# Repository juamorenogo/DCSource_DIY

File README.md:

# EwigVolt - CV/CC Precision DC Supply

---

Electronic design project / UNAL / 2026-1
Project made by:
* Juan Sebastian Moreno Gonzalez
* Nicolás Prieto Solano

## Design Document

It is disposed a PDF file that contains every single detail of the design of this project.

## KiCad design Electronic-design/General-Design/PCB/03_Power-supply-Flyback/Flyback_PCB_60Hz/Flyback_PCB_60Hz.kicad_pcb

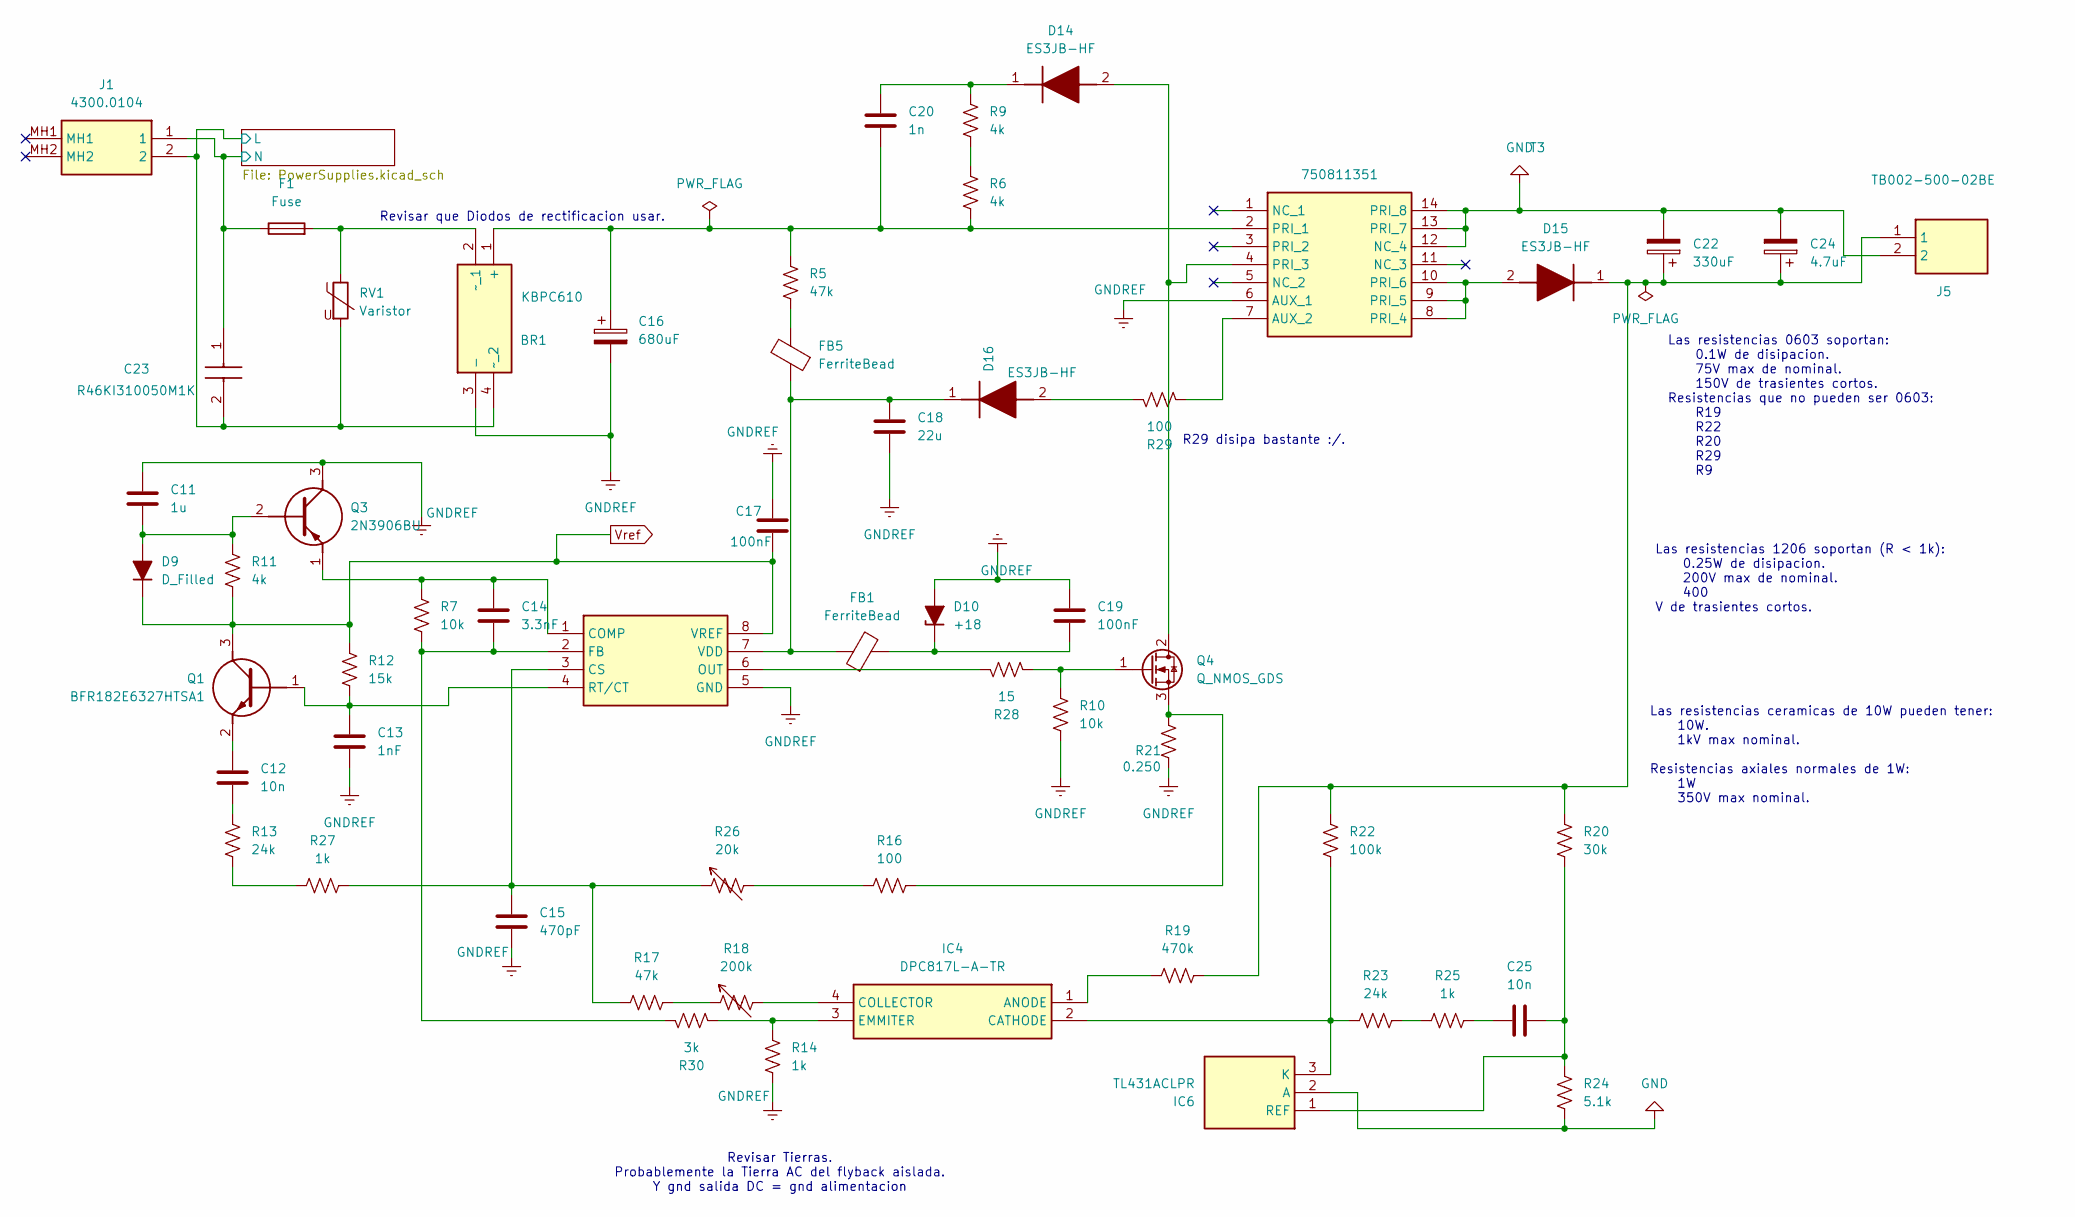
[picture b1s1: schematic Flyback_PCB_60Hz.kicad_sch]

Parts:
BR1: KBPC610; Mouser Part Number 637-KBPC610
C11: 1u; C_0805_2012Metric_Pad1.18x1.45mm_HandSolder
C12, C25: 10n; C_0805_2012Metric_Pad1.18x1.45mm_HandSolder
C13: 1nF; C_0805_2012Metric_Pad1.18x1.45mm_HandSolder
C14: 3.3nF; C_0805_2012Metric_Pad1.18x1.45mm_HandSolder
C15: 470pF; C_0805_2012Metric_Pad1.18x1.45mm_HandSolder
C16: 680uF; CP_Radial_D10.0mm_P5.00mm
C17, C19: 100nF; C_0805_2012Metric_Pad1.18x1.45mm_HandSolder
C18: 22u; CP_Radial_Tantal_D6.0mm_P2.50mm
C20: 1n; C_Disc_D7.5mm_W4.4mm_P5.00mm
C22: 330uF; CP_Radial_D18.0mm_P7.50mm
C23: R46KI310050M1K; Mouser Part Number 80-R46KI310050M1K
C24: 4.7uF; CP_Radial_D10.0mm_P5.00mm
D9: D_Filled; D_SMA_Handsoldering
D10: +18; D_DO-41_SOD81_P10.16mm_Horizontal
D14, D15, D16: ES3JB-HF; DIOM5235X244N; Mouser Part Number 750-ES3JB-HF
F1: Fuse; Fuseholder_Cylinder-5x20mm_Schurter_0031_8201_Horizontal_Op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
FB1, FB5: FerriteBead; BEADC1608X95N
IC4: DPC817L-A-TR; SOP254P1180X410-4N; Manufacturer_Part_Number DPC817L-A-TR
IC5: UCC38C43DR; SOIC127P600X175-8N; Mouser Part Number 595-UCC38C43DR
IC6: TL431ACLPR; Mouser Part Number 595-TL431ACLPR
J1: 4300.0104; 43000104; Mouser Part Number 693-4300.0104
J5: TB002-500-02BE; Mouser Part Number 490-TB002-500-02BE
Q1: BFR182E6327HTSA1; NPN_SOT95P240X110-3N; Manufacturer_Part_Number BFR182E6327HTSA1
Q3: 2N3906BU; Mouser Part Number 512-2N3906BU
Q4: Q_NMOS_GDS; TO-220F-3_Vertical
R5, R17: 47k; R_0603_1608Metric_Pad0.98x0.95mm_HandSolder
R6, R9: 4k; R_Axial_Power_L20.0mm_W6.4mm_P25.40mm
R7, R10: 10k; R_0603_1608Metric_Pad0.98x0.95mm_HandSolder
R11: 4k; R_0603_1608Metric_Pad0.98x0.95mm_HandSolder
R12: 15k; R_0603_1608Metric_Pad0.98x0.95mm_HandSolder
R13, R23: 24k; R_0603_1608Metric_Pad0.98x0.95mm_HandSolder
R14, R25, R27: 1k; R_0603_1608Metric_Pad0.98x0.95mm_HandSolder
R16: 100; R_1206_3216Metric_Pad1.30x1.75mm_HandSolder
R18: 200k; Potentiometer_Bourns_3296W_Vertical
R19: 470k; R_1206_3216Metric_Pad1.30x1.75mm_HandSolder
R20: 30k; R_Axial_DIN0414_L11.9mm_D4.5mm_P15.24mm_Horizontal
R21: 0.250; RESC6432X70N
R22: 100k; R_Axial_DIN0414_L11.9mm_D4.5mm_P15.24mm_Horizontal
R24: 5.1k; R_1206_3216Metric_Pad1.30x1.75mm_HandSolder
R26: 20k; Potentiometer_Bourns_3296W_Vertical
R28: 15; R_1206_3216Metric_Pad1.30x1.75mm_HandSolder
R29: 100; R_Axial_DIN0414_L11.9mm_D4.5mm_P15.24mm_Horizontal
R30: 3k; R_0603_1608Metric_Pad0.98x0.95mm_HandSolder
RV1: Varistor; RV_Disc_D15.5mm_W4.4mm_P7.5mm
T3: 750811351; Mouser Part Number 710-750811351

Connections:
/Supplies/L: BR1.4 (~_2), C23.2, J1.2, RV1.2; also elsewhere on the board
/Supplies/N: C23.1, F1.1, J1.1; also elsewhere on the board
GND: C22.2, C24.2, IC6.2 (A), J5.2, R24.2, T3.12 (NC_4), T3.13 (PRI_7), T3.14 (PRI_8); also elsewhere on the board
GNDREF: BR1.3 (-), C11.1, C13.2, C15.2, C16.2, C17.1, C18.2, C19.1, D10.2 (A), IC5.5 (GND), Q3.3 (C), R10.2, R14.2, R21.2, T3.6 (AUX_1)
unnamed: BR1.1 (+), C16.1, C20.2, R5.1, R6.2, T3.2 (PRI_1)
unnamed: BR1.2 (~_1), F1.2, RV1.1
unnamed: C12.2, R13.1
unnamed: C25.2, R25.1
unnamed: C11.2, D9.2 (A), Q3.2 (B), R11.1
unnamed: C19.2, D10.1 (K), FB1.2
unnamed: D14.2 (A), Q4.2 (D), T3.4 (PRI_3)
unnamed: C20.1, D14.1 (K), R9.1
unnamed: D15.2 (A), T3.8 (PRI_4), T3.9 (PRI_5), T3.10 (PRI_6)
unnamed: C22.1, C24.1, D15.1 (K), J5.1, R19.1, R20.1, R22.2
unnamed: D16.2 (A), R29.1
unnamed: C18.1, D16.1 (K), FB1.1, FB5.1, IC5.7 (VDD)
unnamed: FB5.2, R5.2
unnamed: IC4.1 (ANODE), R19.2
unnamed: IC4.2 (CATHODE), IC6.3 (K), R22.1, R23.2
unnamed: IC4.4 (COLLECTOR), R18.2
unnamed: IC4.3 (EMMITER), R14.1, R30.2
unnamed: C14.1, IC5.1 (COMP), Q3.1 (E), R7.1
unnamed: C15.1, IC5.3 (CS), R17.1, R26.1, R27.2
unnamed: C14.2, IC5.2 (FB), R7.2, R30.1
unnamed: IC5.6 (OUT), R28.1
unnamed: C13.1, IC5.4 (RT/CT), Q1.1 (B), R12.2
unnamed: C25.1, IC6.1 (REF), R20.2, R24.1
unnamed: C12.1, Q1.2 (E)
unnamed: Q4.1 (G), R10.1, R28.2
unnamed: Q4.3 (S), R16.2, R21.1
unnamed: R6.1, R9.2
unnamed: R13.2, R27.1
unnamed: R16.1, R26.2
unnamed: R17.2, R18.1
unnamed: R23.1, R25.2
unnamed: R29.2, T3.7 (AUX_2)
Vref: C17.2, D9.1 (K), IC5.8 (VREF), Q1.3 (C), R11.2, R12.1

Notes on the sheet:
Las resistencias 1206 soportan (R < 1k): 0.25W de disipacion. 200V max de nominal. 400 V de trasientes cortos.
Revisar Tierras. Probablemente la Tierra AC del flyback aislada. Y gnd salida DC = gnd alimentacion
Las resistencias ceramicas de 10W pueden tener: 10W. 1kV max nominal. Resistencias axiales normales de 1W: 1W 350V max nominal.
R29 disipa bastante :/.
Las resistencias 0603 soportan: 0.1W de disipacion. 75V max de nominal. 150V de trasientes cortos. Resistencias que no pueden ser 0603: R19 R22 R20 R29 R9
Revisar que Diodos de rectificacion usar.

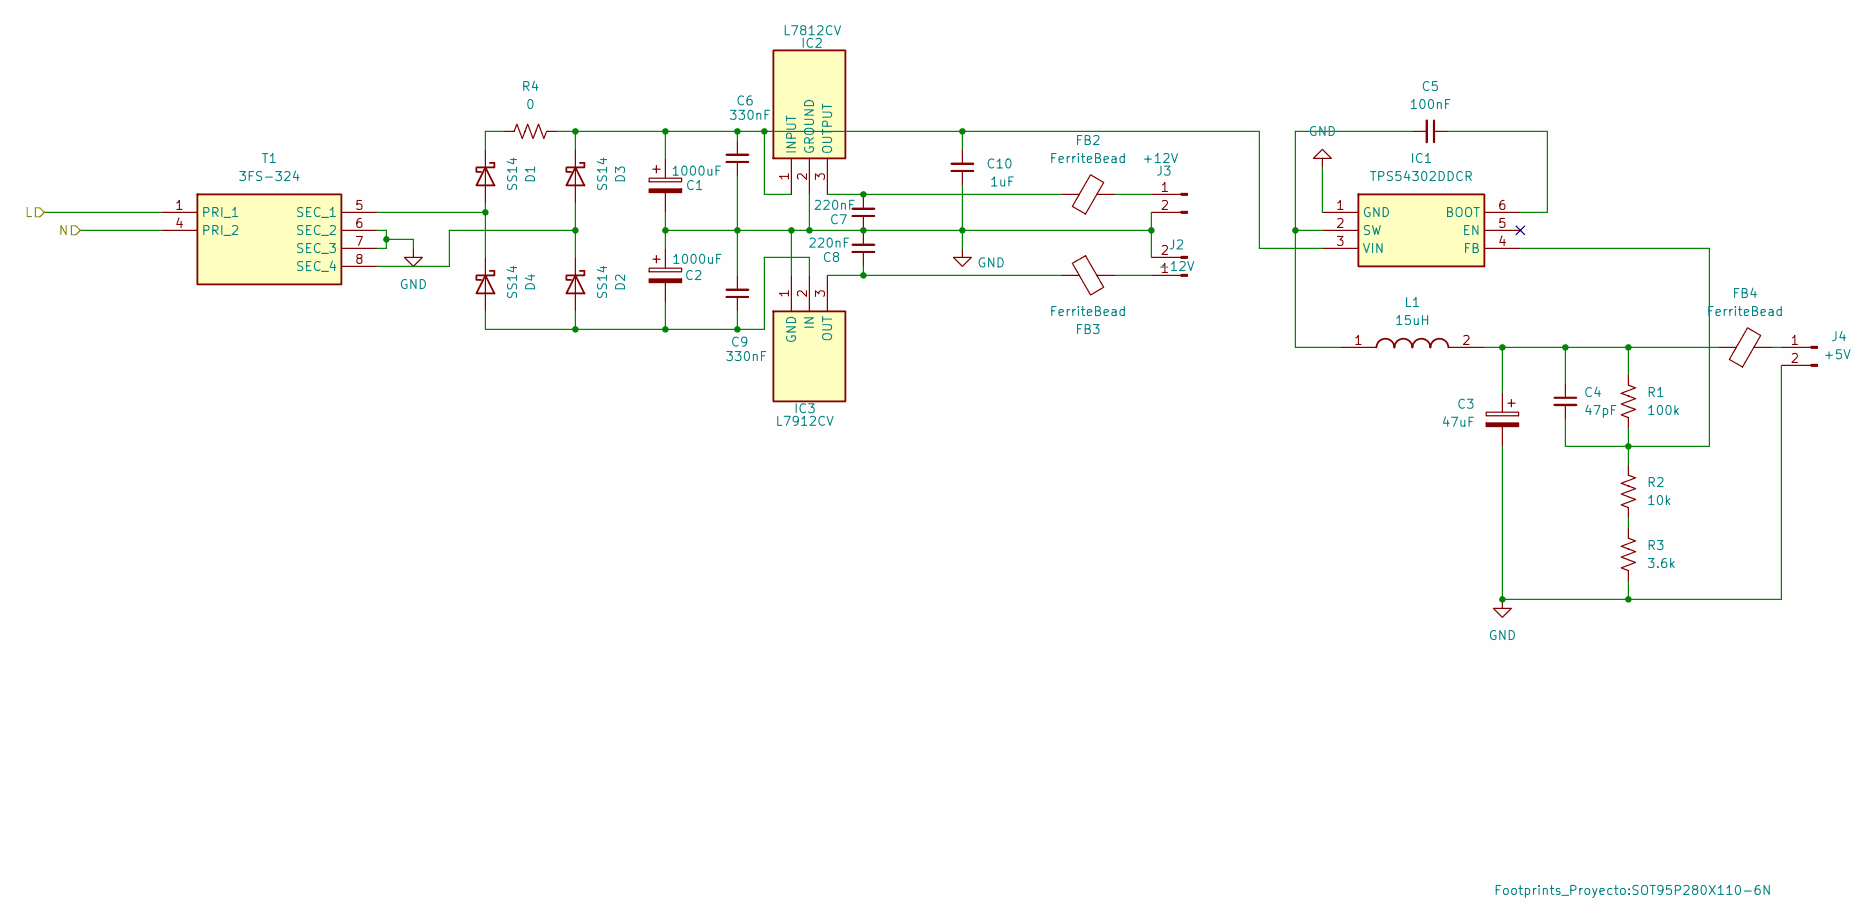
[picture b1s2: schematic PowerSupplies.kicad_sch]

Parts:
C1, C2: 1000uF; CP_Radial_D10.0mm_P5.00mm
C3: 47uF; CP_Radial_D6.3mm_P2.50mm
C4: 47pF; C_0805_2012Metric_Pad1.18x1.45mm_HandSolder
C5: 100nF; C_0805_2012Metric_Pad1.18x1.45mm_HandSolder
C6, C9: 330nF; C_0805_2012Metric_Pad1.18x1.45mm_HandSolder
C7, C8: 220nF; C_0805_2012Metric_Pad1.18x1.45mm_HandSolder
C10: 1uF; C_0805_2012Metric_Pad1.18x1.45mm_HandSolder
D1, D2, D3, D4: SS14; D_SMA
FB2, FB3, FB4: FerriteBead; BEADC1608X95N
IC1: TPS54302DDCR; SOT95P280X110-6N; Mouser Part Number 595-TPS54302DDCR
IC2: L7812CV; L8_TO255P460X1020X2008-3P; Mouser Part Number 511-L7812CV
IC3: L7912CV; L9_TO255P460X1020X2008-3P; Mouser Part Number 511-L7912CV
J2: -12V; PinHeader_1x02_P2.54mm_Vertical
J3: +12V; PinHeader_1x02_P2.54mm_Vertical
J4: +5V; PinHeader_1x02_P2.54mm_Vertical
L1: 15uH; INDPM116102X400N; Manufacturer_Part_Number AMRM00101040150MA1
R1: 100k; R_0603_1608Metric_Pad0.98x0.95mm_HandSolder
R2: 10k; R_0603_1608Metric_Pad0.98x0.95mm_HandSolder
R3: 3.6k; R_0603_1608Metric_Pad0.98x0.95mm_HandSolder
R4: 0; R_1210_3225Metric_Pad1.30x2.65mm_HandSolder
T1: 3FS-324; 3FS324; Mouser Part Number 838-3FS-324

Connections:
/Supplies/L: T1.1 (PRI_1); also elsewhere on the board
/Supplies/N: T1.4 (PRI_2); also elsewhere on the board
GND: C1.2, C2.1, C3.2, C6.1, C7.1, C8.2, C9.2, C10.1, IC1.1 (GND), IC2.2 (GROUND), IC3.1 (GND), J2.2, J3.2, J4.2, R3.2, T1.6 (SEC_2), T1.7 (SEC_3); also elsewhere on the board
unnamed: C3.1, C4.1, FB4.1, L1.2, R1.1
unnamed: D1.2 (A), D4.1 (K), T1.5 (SEC_1)
unnamed: D1.1 (K), R4.1
unnamed: C2.2, C9.1, D2.2 (A), D4.2 (A), IC3.2 (IN)
unnamed: D2.1 (K), D3.2 (A), T1.8 (SEC_4)
unnamed: C1.1, C6.2, C10.2, D3.1 (K), IC1.3 (VIN), IC2.1 (INPUT), R4.2
unnamed: C5.1, IC1.6 (BOOT)
unnamed: C4.2, IC1.4 (FB), R1.2, R2.1
unnamed: C5.2, IC1.2 (SW), L1.1
unnamed: C7.2, FB2.1, IC2.3 (OUTPUT)
unnamed: C8.1, FB3.1, IC3.3 (OUT)
unnamed: FB3.2, J2.1
unnamed: FB2.2, J3.1
unnamed: FB4.2, J4.1
unnamed: R2.2, R3.1

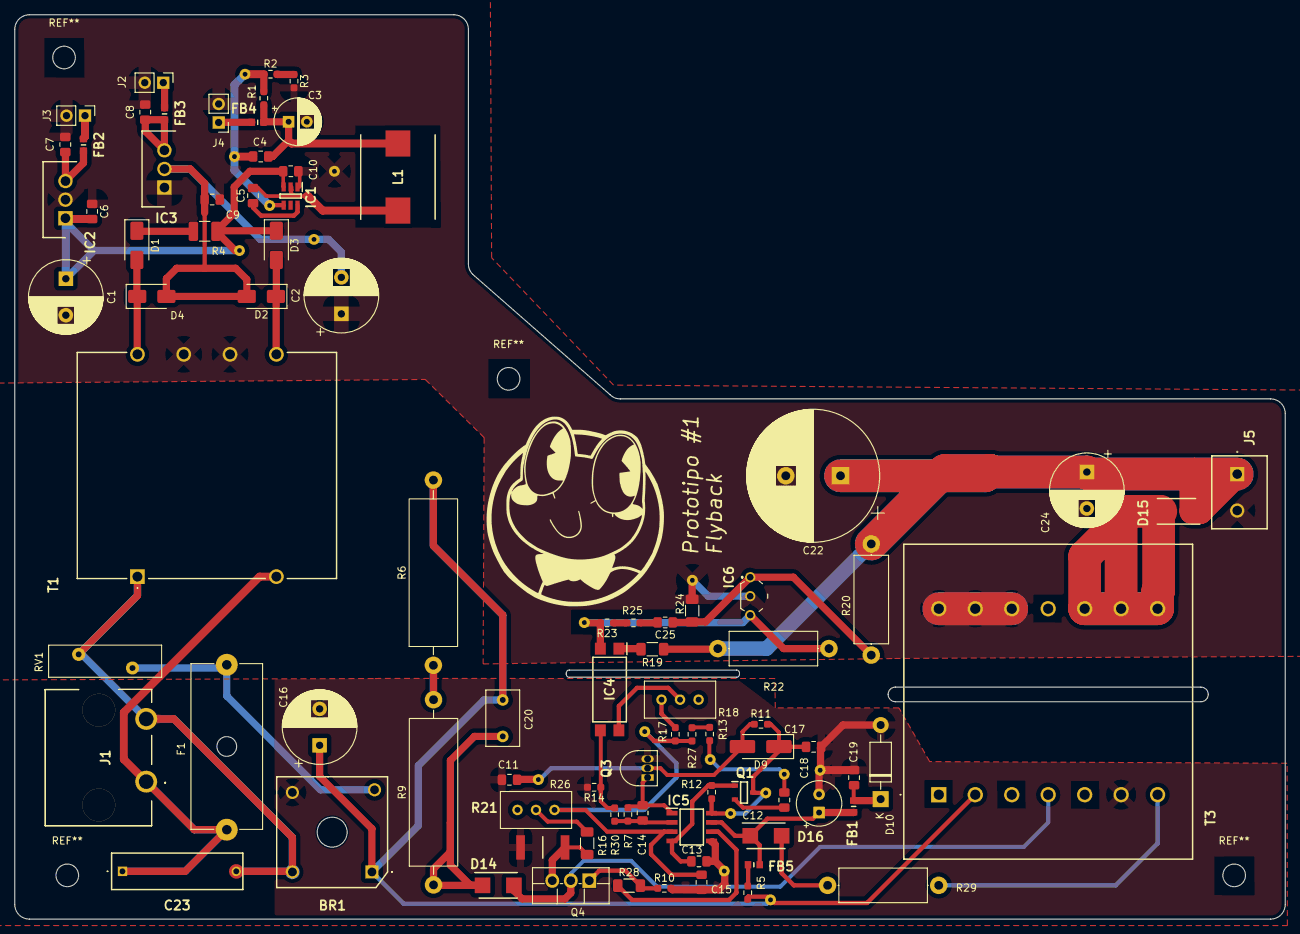
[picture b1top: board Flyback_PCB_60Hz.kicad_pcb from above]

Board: 2 copper layers, 174.2 x 124.0 mm, 86 parts (0 on the bottom side), 52 nets.

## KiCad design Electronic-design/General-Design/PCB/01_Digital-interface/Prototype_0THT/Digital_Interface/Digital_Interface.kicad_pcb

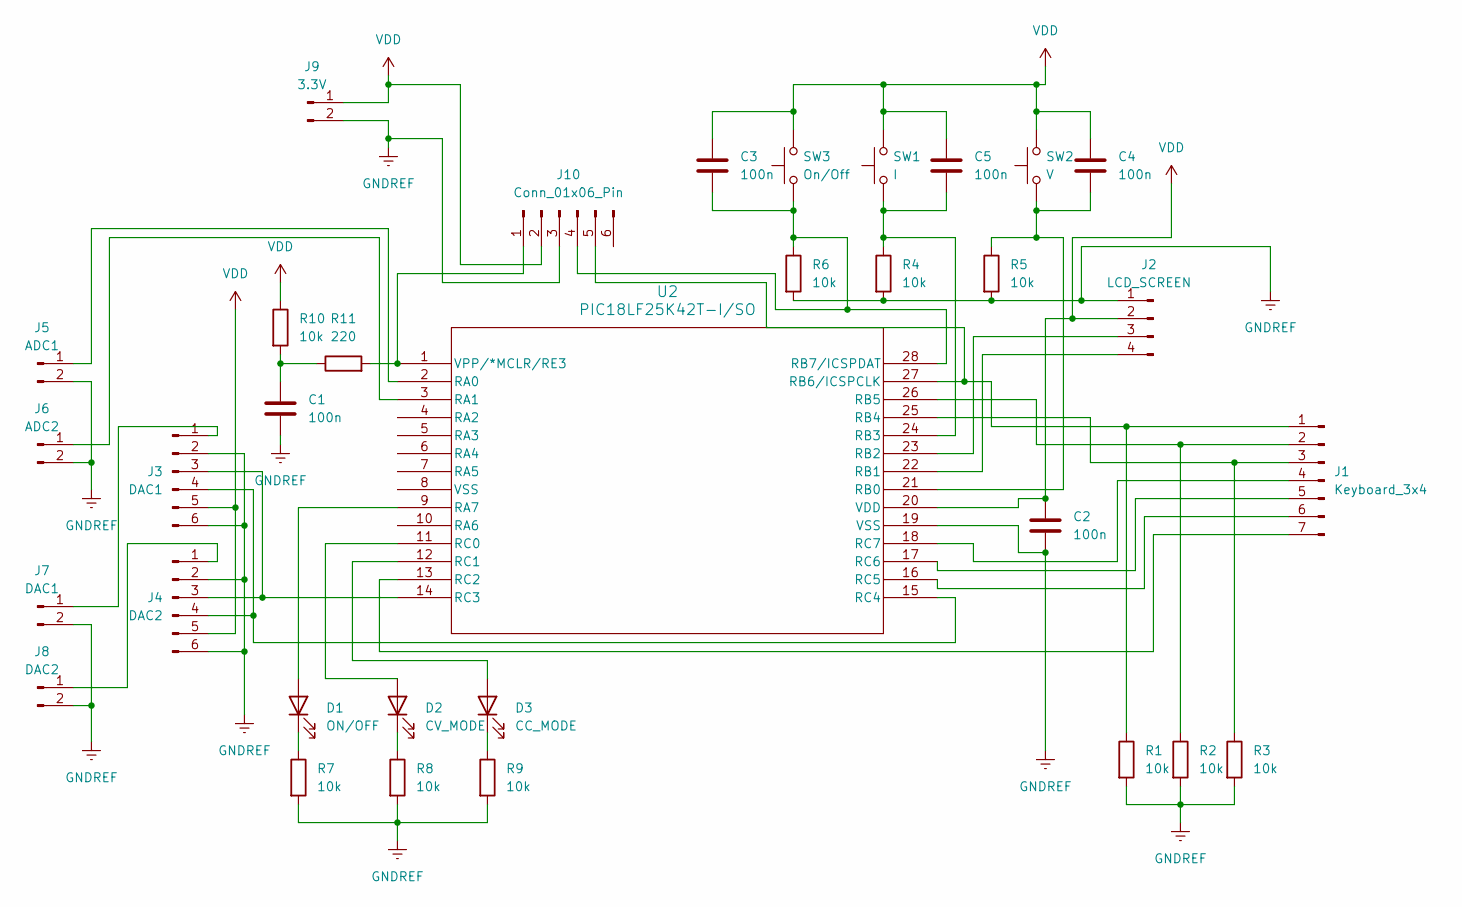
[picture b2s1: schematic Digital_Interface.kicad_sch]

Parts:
C1, C2, C3, C4, C5: 100n; C_Disc_D5.0mm_W2.5mm_P5.00mm
D1: ON/OFF; LED_D5.0mm
D2: CV_MODE; LED_D5.0mm
D3: CC_MODE; LED_D5.0mm
J1: Keyboard_3x4; PinHeader_1x07_P2.54mm_Vertical
J2: LCD_SCREEN; PinHeader_1x04_P2.54mm_Vertical
J3: DAC1; MCP4725_module
J4: DAC2; MCP4725_module
J5: ADC1; PinHeader_1x02_P2.54mm_Vertical
J6: ADC2; PinHeader_1x02_P2.54mm_Vertical
J7: DAC1; PinHeader_1x02_P2.54mm_Vertical
J8: DAC2; PinHeader_1x02_P2.54mm_Vertical
J9: 3.3V; PinHeader_1x02_P2.54mm_Vertical
J10: Conn_01x06_Pin; PinHeader_1x06_P2.54mm_Vertical
R1, R2, R3, R4, R5, R6, R7, R8, R9, R10: 10k; R_Axial_DIN0207_L6.3mm_D2.5mm_P7.62mm_Horizontal
R11: 220; R_Axial_DIN0207_L6.3mm_D2.5mm_P7.62mm_Horizontal
SW1: I; SW_PUSH_6mm
SW2: V; SW_PUSH_6mm
SW3: On/Off; SW_PUSH_6mm
U2: PIC18LF25K42T-I/SO; SOIC28_SO_MCH

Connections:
GNDREF: C1.2, C2.2, J2.1, J3.2, J3.6, J4.2, J4.6, J5.2, J6.2, J7.2, J8.2, J9.2, J10.3, R1.2, R2.2, R3.2, R4.2, R5.2, R6.2, R7.2, R8.2, R9.2, U2.19 (VSS)
unnamed: C1.1, R10.2, R11.1
unnamed: D1.2 (A), U2.9 (RA7)
unnamed: D1.1 (K), R7.1
unnamed: D2.2 (A), U2.11 (RC0)
unnamed: D2.1 (K), R8.1
unnamed: D3.2 (A), U2.12 (RC1)
unnamed: D3.1 (K), R9.1
unnamed: J1.1, J10.5, R1.1, U2.27 (RB6/ICSPCLK)
unnamed: J1.2, R2.1, U2.26 (RB5)
unnamed: J1.3, R3.1, U2.25 (RB4)
unnamed: J1.4, U2.18 (RC7)
unnamed: J1.5, U2.17 (RC6)
unnamed: J1.6, U2.16 (RC5)
unnamed: J1.7, U2.13 (RC2)
unnamed: J2.3, U2.23 (RB2)
unnamed: J2.4, U2.22 (RB1)
unnamed: J3.1, J7.1
unnamed: J3.3, J4.3, U2.14 (RC3)
unnamed: J3.4, J4.4, U2.15 (RC4)
unnamed: J4.1, J8.1
unnamed: J5.1, U2.2 (RA0)
unnamed: J6.1, U2.3 (RA1)
unnamed: J10.1, R11.2, U2.1 (VPP/*MCLR/RE3)
unnamed: C3.2, J10.4, R6.1, SW3.1, U2.28 (RB7/ICSPDAT)
unnamed: C4.2, R5.1, SW2.1, U2.21 (RB0)
unnamed: C5.2, R4.1, SW1.1, U2.24 (RB3)
VDD: C2.1, C3.1, C4.1, C5.1, J2.2, J3.5, J4.5, J9.1, J10.2, R10.1, SW1.2, SW2.2, SW3.2, U2.20 (VDD)

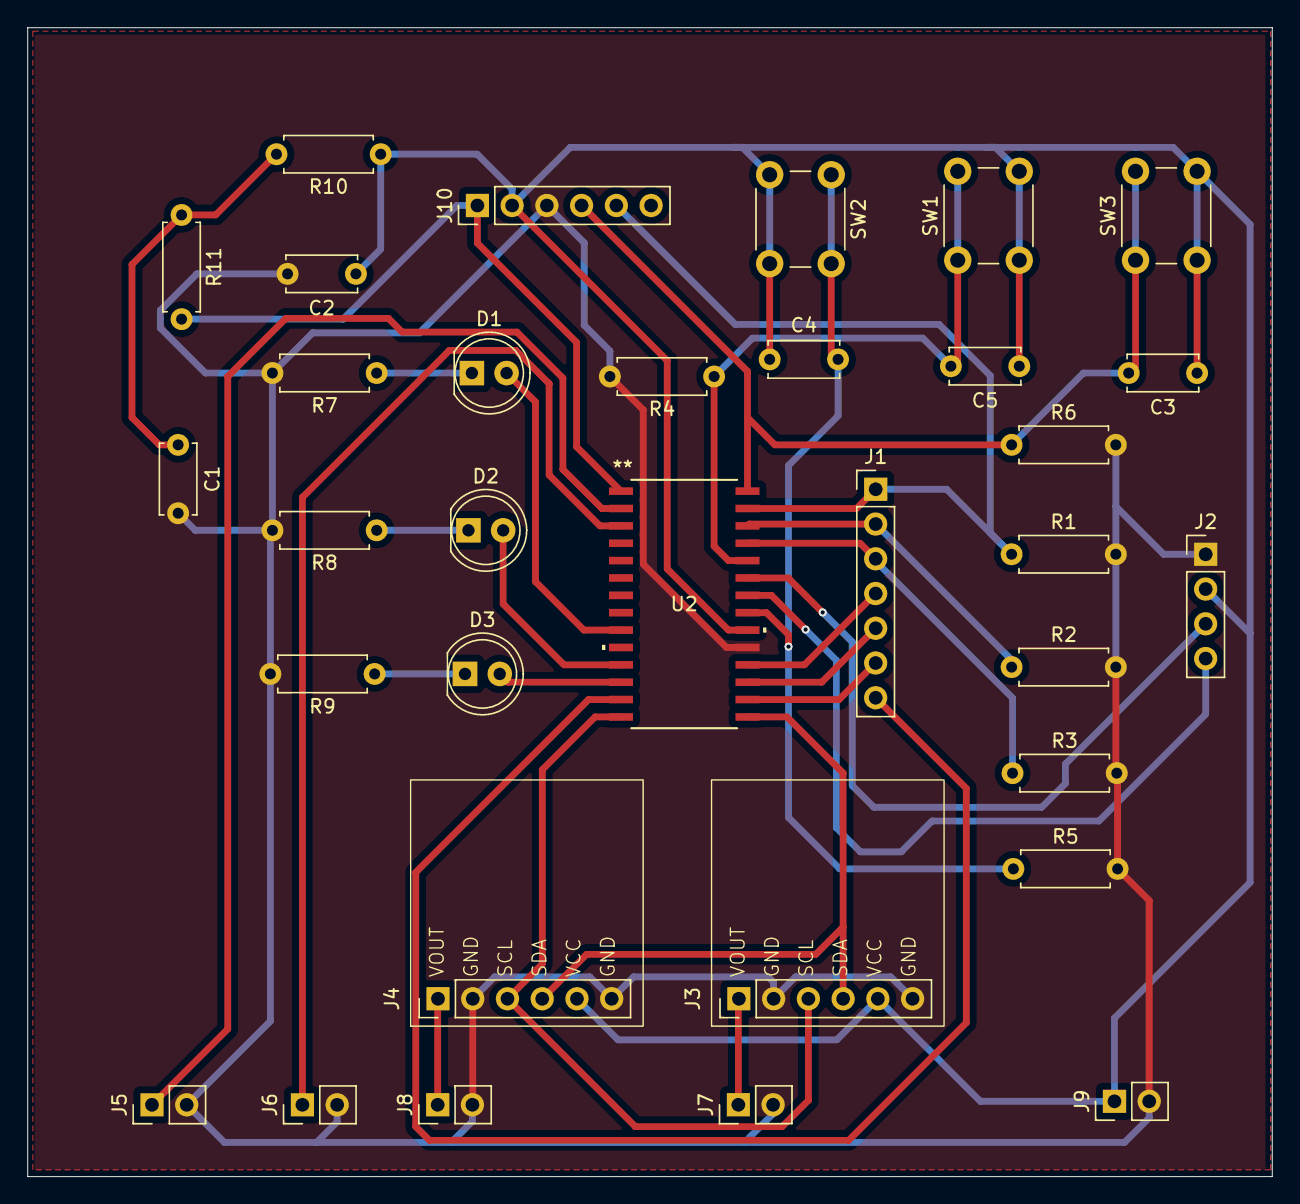
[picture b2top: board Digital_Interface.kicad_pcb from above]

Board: 2 copper layers, 91.0 x 84.0 mm, 33 parts (0 on the bottom side), 28 nets.

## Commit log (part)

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2026-02-22 DESKTOP-D4K75HQ 2026-2-22:18:13:4
2026-02-22 DESKTOP-D4K75HQ 2026-2-22:18:13:18
2026-02-23 DiagramaBloques
2026-02-23 DiagramaBloques2
2026-02-23 DiagramaBloques3
2026-02-23 DiagramaBloques4
2026-02-23 Update README.md with requirements.
2026-02-23 Prueba github en terminal
2026-02-23 Added requirements and restrictions.
2026-02-23 Added presupuesto
2026-02-24 Bullshit
2026-02-24 Bloques3
2026-03-01 v1_1_0
2026-03-01 v1_1_0a
2026-03-01 v1_1_0b
2026-03-01 v1_1_0c
2026-03-01 v1_1_0d
2026-03-01 v1_1_0e
2026-03-01 v1_1_0f
2026-03-01 documentacion1
2026-03-01 documentacion2
2026-03-01 documentacion3
2026-03-01 documentacion4
2026-03-01 documentacion5
2026-03-07 correcionNombres
2026-03-07 obsidian_modification
2026-04-07 Teoria para medicion de corriente 1
2026-04-07 Teoria para medicion de corriente 2
2026-04-07 Ewigvolt
2026-04-23 Added protocolo de validacion.
2026-04-29 Addeded requeriments, this time yes.
2026-05-10 Ajuste-carpetas-y-pdf
2026-05-10 Folders-adjust-09 of May
2026-05-10 english
2026-05-10 fix-some-readmes
2026-05-10 Ltspice-model
2026-05-10 Underlight-UCC-Datasheet1
2026-05-11 PDF-UCC-underlight-2
2026-05-12 LTSpice-circuit-ohne-values
2026-05-12 Python-calcs-1
2026-05-12 Snubber
2026-05-12 Python-calcs-2
2026-05-23 PSIM-simulation-test1
2026-05-24 PSIM-simulation-2test
2026-05-24 add gitignore
2026-05-24 Delete-esc2
2026-05-24 Python-calcs2
2026-05-25 Python-calcs-almost-complete
2026-05-25 PSIM-python-values-test1
2026-05-25 Al menos saca 30V :(
2026-05-26 Kicad-Schematic-Flyback1
2026-05-26 Added digital interface
2026-05-26 Added kiCad
2026-05-26 Tests-PSIM
2026-05-27 PSIM-More-Watts
2026-05-28 AHHHHHHHHHHHHHHHHH
2026-05-30 PSIM-final-elements-Test1
2026-06-08 Added test digital interface PCB
